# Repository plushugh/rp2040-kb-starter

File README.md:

# A Keyboard PCB Starter for the RaspberrySilicon RP2040 Microcontroller

## KiCad Requirements

I recommend KiCad version >= 8.0, and make sure you install the
[kiswitch](https://github.com/kiswitch/kiswitch) plugin (Version 2.4)
from the `Plugin and Content Manager`

I also recommend installing the kbplacer plugin for easy alignment of switch footprints

## Credits

Inspired by [Sleepdealr/RP2040-designguide](https://github.com/Sleepdealr/RP2040-designguide?tab=readme-ov-file)

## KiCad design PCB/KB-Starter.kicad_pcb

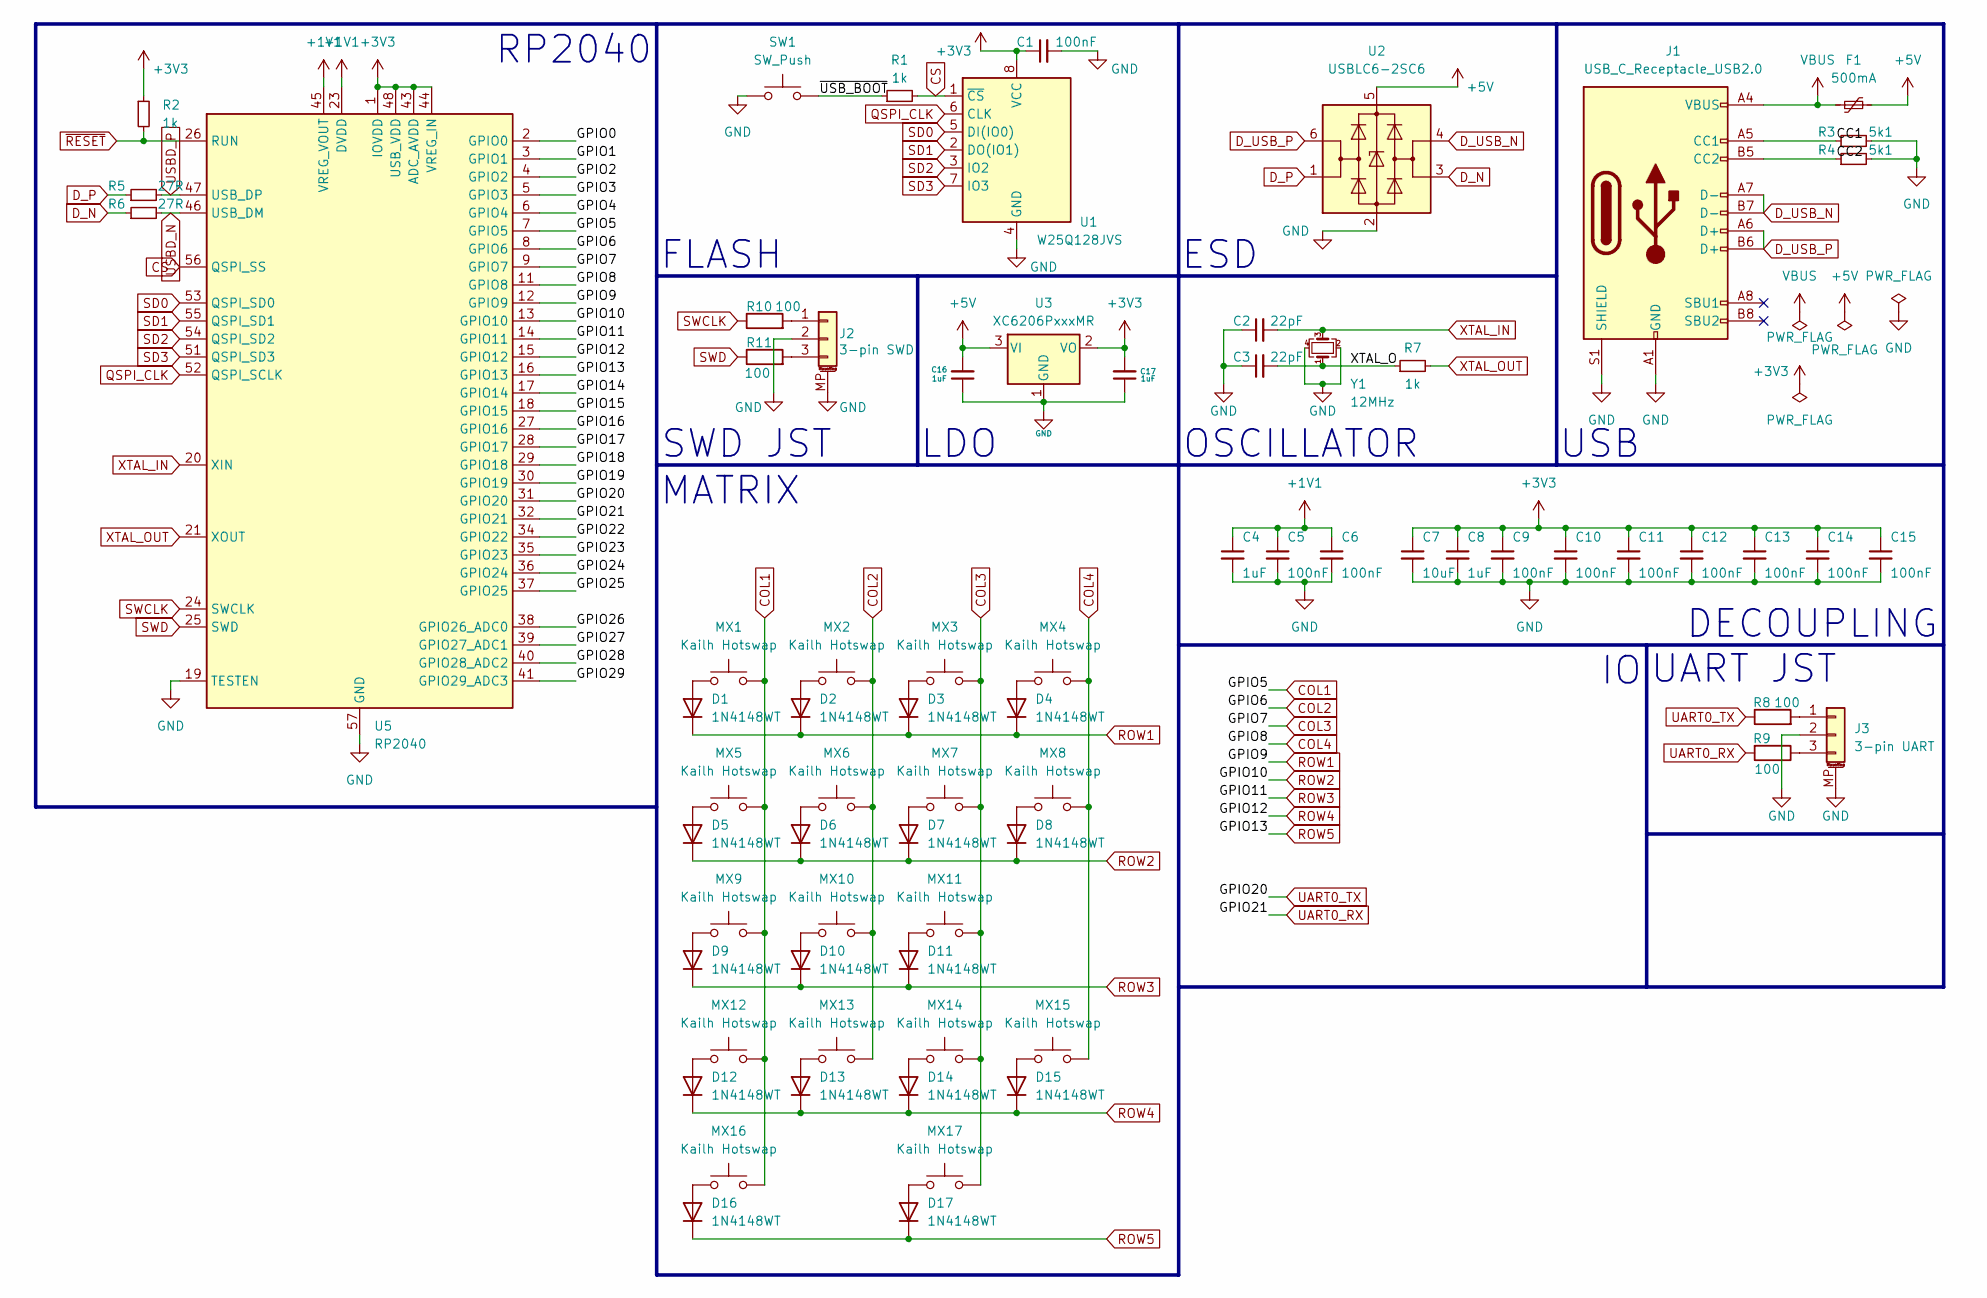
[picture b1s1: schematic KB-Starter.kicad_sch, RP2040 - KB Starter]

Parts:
C1, C5, C6, C9, C10, C11, C12, C13, C14, C15: 100nF; C_0402_1005Metric; LCSC C1525
C2, C3: 22pF; C_0402_1005Metric; LCSC C1555
C4, C8, C16, C17: 1uF; C_0402_1005Metric; LCSC C52923
C7: 10uF; C_0402_1005Metric; LCSC C15525
D1, D2, D3, D4, D5, D6, D7, D8, D9, D10, D11, D12, D13, D14, D15, D16, D17: 1N4148WT; D_SOD-523; LCSC C727112
F1: 500mA; Fuse_1206_3216Metric; LCSC C70076
J1: USB_C_Receptacle_USB2.0; USB_C_Receptacle_HRO_TYPE-C-31-M-12; LCSC C165948
J2: 3-pin SWD; JST_SH_BM03B-SRSS-TB_1x03-1MP_P1.00mm_Vertical
J3: 3-pin UART; JST_SH_BM03B-SRSS-TB_1x03-1MP_P1.00mm_Vertical
MX1, MX2, MX3, MX4, MX5, MX6, MX7, MX8, MX9, MX10, MX11, MX12, MX13, MX14, MX15, MX16, MX17: Kailh Hotswap; SW_Hotswap_Kailh_MX_1.00u; LCSC C5156480
R1, R2, R7: 1k; R_0402_1005Metric; LCSC C11702
R3, R4: 5k1; R_0402_1005Metric; LCSC C25905
R5, R6: 27R; R_0603_1608Metric; LCSC C25190
R8, R9, R10, R11: 100; R_0603_1608Metric
SW1: SW_Push; SW_SPST_PTS810; LCSC C221896
U1: W25Q128JVS; SOIC-8_5.23x5.23mm_P1.27mm; LCSC C131025
U2: USBLC6-2SC6; SOT-23-6; LCSC C2827654
U3: XC6206PxxxMR; SOT-23-3; LCSC C5250982
U5: RP2040; QFN-56-1EP_7x7mm_P0.4mm_EP3.2x3.2mm; LCSC C2040
Y1: 12MHz; Crystal_SMD_3225-4Pin_3.2x2.5mm; LCSC C9002

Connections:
+1V1: C4.1, C5.1, C6.1, U5.23 (DVDD), U5.45 (VREG_VOUT), U5.50 (DVDD)
+3V3: C1.1, C7.1, C8.1, C9.1, C10.1, C11.1, C12.1, C13.1, C14.1, C15.1, C17.2, R2.1, U1.8 (VCC), U3.2 (VO), U5.1 (IOVDD), U5.10 (IOVDD), U5.22 (IOVDD), U5.33 (IOVDD), U5.42 (IOVDD), U5.43 (ADC_AVDD), U5.44 (VREG_IN), U5.48 (USB_VDD), U5.49 (IOVDD)
+5V: C16.2, F1.2, U2.5 (VBUS), U3.3 (VI)
/CC1: J1.A5 (CC1), R3.1
/CC2: J1.B5 (CC2), R4.1
/GPIO0: U5.2 (GPIO0)
/GPIO1: U5.3 (GPIO1)
/GPIO2: U5.4 (GPIO2)
/GPIO3: U5.5 (GPIO3)
/GPIO4: U5.6 (GPIO4)
/GPIO14: U5.17 (GPIO14)
/GPIO15: U5.18 (GPIO15)
/GPIO16: U5.27 (GPIO16)
/GPIO17: U5.28 (GPIO17)
/GPIO18: U5.29 (GPIO18)
/GPIO19: U5.30 (GPIO19)
/GPIO22: U5.34 (GPIO22)
/GPIO23: U5.35 (GPIO23)
/GPIO24: U5.36 (GPIO24)
/GPIO25: U5.37 (GPIO25)
/GPIO26: U5.38 (GPIO26_ADC0)
/GPIO27: U5.39 (GPIO27_ADC1)
/GPIO28: U5.40 (GPIO28_ADC2)
/GPIO29: U5.41 (GPIO29_ADC3)
/XTAL_O: C3.2, R7.1, Y1.1
/~USB_BOOT: R1.1, SW1.2
COL1: MX1.2, MX5.2, MX9.2, MX12.2, MX16.2, U5.7 (GPIO5)
COL2: MX2.2, MX6.2, MX10.2, MX13.2, U5.8 (GPIO6)
COL3: MX3.2, MX7.2, MX11.2, MX14.2, MX17.2, U5.9 (GPIO7)
COL4: MX4.2, MX8.2, MX15.2, U5.11 (GPIO8)
CS: R1.2, U1.1 (~CS), U5.56 (QSPI_SS)
D_N: R6.1, U2.3 (I/O2)
D_P: R5.1, U2.1 (I/O1)
D_USB_N: J1.A7 (D-), J1.B7 (D-), U2.4 (I/O2)
D_USB_P: J1.A6 (D+), J1.B6 (D+), U2.6 (I/O1)
GND: C1.2, C2.1, C3.1, C4.2, C5.2, C6.2, C7.2, C8.2, C9.2, C10.2, C11.2, C12.2, C13.2, C14.2, C15.2, C16.1, C17.1, J1.A1 (GND), J1.A12 (GND), J1.B1 (GND), J1.B12 (GND), J1.S1 (SHIELD), J2.2, J2.MP (MountPin), J3.2, J3.MP (MountPin), R3.2, R4.2, SW1.1, U1.4 (GND), U2.2 (GND), U3.1 (GND), U5.19 (TESTEN), U5.57 (GND), Y1.2, Y1.4
unnamed: D1.2 (A), MX1.1
unnamed: D2.2 (A), MX2.1
unnamed: D3.2 (A), MX3.1
unnamed: D4.2 (A), MX4.1
unnamed: D5.2 (A), MX5.1
unnamed: D6.2 (A), MX6.1
unnamed: D7.2 (A), MX7.1
unnamed: D8.2 (A), MX8.1
unnamed: D9.2 (A), MX9.1
unnamed: D10.2 (A), MX10.1
unnamed: D11.2 (A), MX11.1
unnamed: D12.2 (A), MX12.1
unnamed: D13.2 (A), MX13.1
unnamed: D14.2 (A), MX14.1
unnamed: D15.2 (A), MX15.1
unnamed: D16.2 (A), MX16.1
unnamed: D17.2 (A), MX17.1
unnamed: J2.1, R10.2
unnamed: J2.3, R11.2
unnamed: J3.1, R8.2
unnamed: J3.3, R9.1
QSPI_CLK: U1.6 (CLK), U5.52 (QSPI_SCLK)
ROW1: D1.1 (K), D2.1 (K), D3.1 (K), D4.1 (K), U5.12 (GPIO9)
ROW2: D5.1 (K), D6.1 (K), D7.1 (K), D8.1 (K), U5.13 (GPIO10)
ROW3: D9.1 (K), D10.1 (K), D11.1 (K), U5.14 (GPIO11)
ROW4: D12.1 (K), D13.1 (K), D14.1 (K), D15.1 (K), U5.15 (GPIO12)
ROW5: D16.1 (K), D17.1 (K), U5.16 (GPIO13)
SD0: U1.5 (DI(IO0)), U5.53 (QSPI_SD0)
SD1: U1.2 (DO(IO1)), U5.55 (QSPI_SD1)
SD2: U1.3 (IO2), U5.54 (QSPI_SD2)
SD3: U1.7 (IO3), U5.51 (QSPI_SD3)
SWCLK: R10.1, U5.24 (SWCLK)
SWD: R11.1, U5.25 (SWD)
UART0_RX: R9.2, U5.32 (GPIO21)
UART0_TX: R8.1, U5.31 (GPIO20)
USBD_N: R6.2, U5.46 (USB_DM)
USBD_P: R5.2, U5.47 (USB_DP)
VBUS: F1.1, J1.A4 (VBUS), J1.A9 (VBUS), J1.B4 (VBUS), J1.B9 (VBUS)
XTAL_IN: C2.2, U5.20 (XIN), Y1.3
XTAL_OUT: R7.2, U5.21 (XOUT)
~RESET: R2.2, U5.26 (RUN)

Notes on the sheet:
MATRIX
ESD
UART JST
DECOUPLING
OSCILLATOR
USB
LDO
SWD JST
RP2040
FLASH

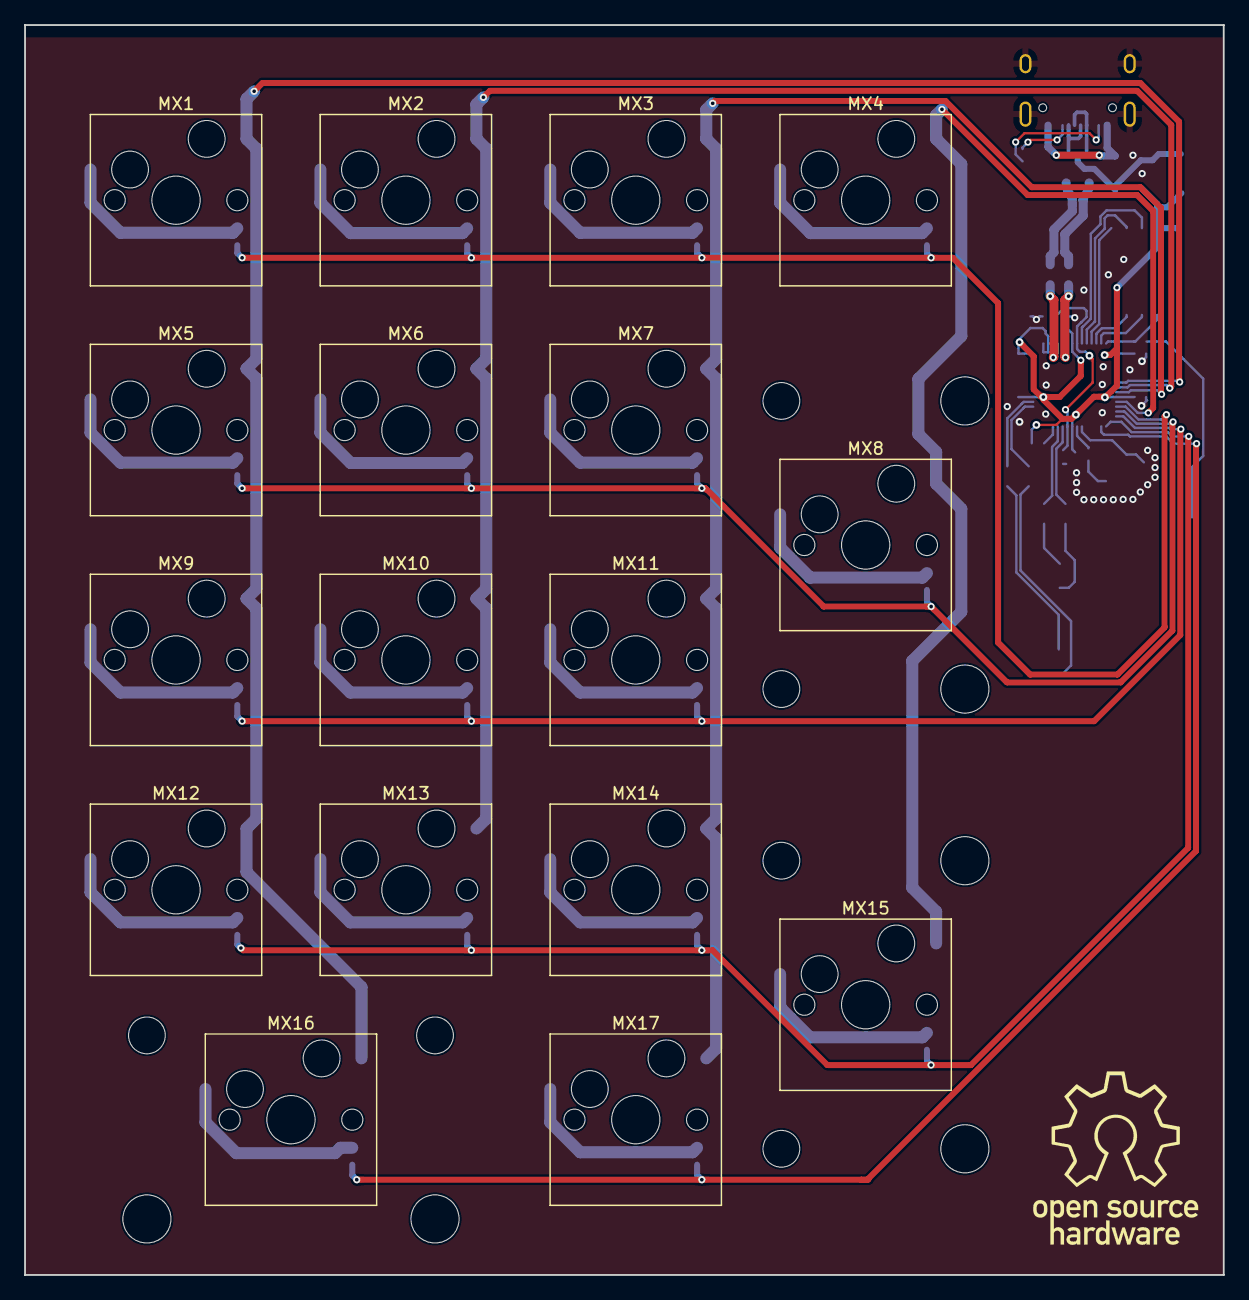
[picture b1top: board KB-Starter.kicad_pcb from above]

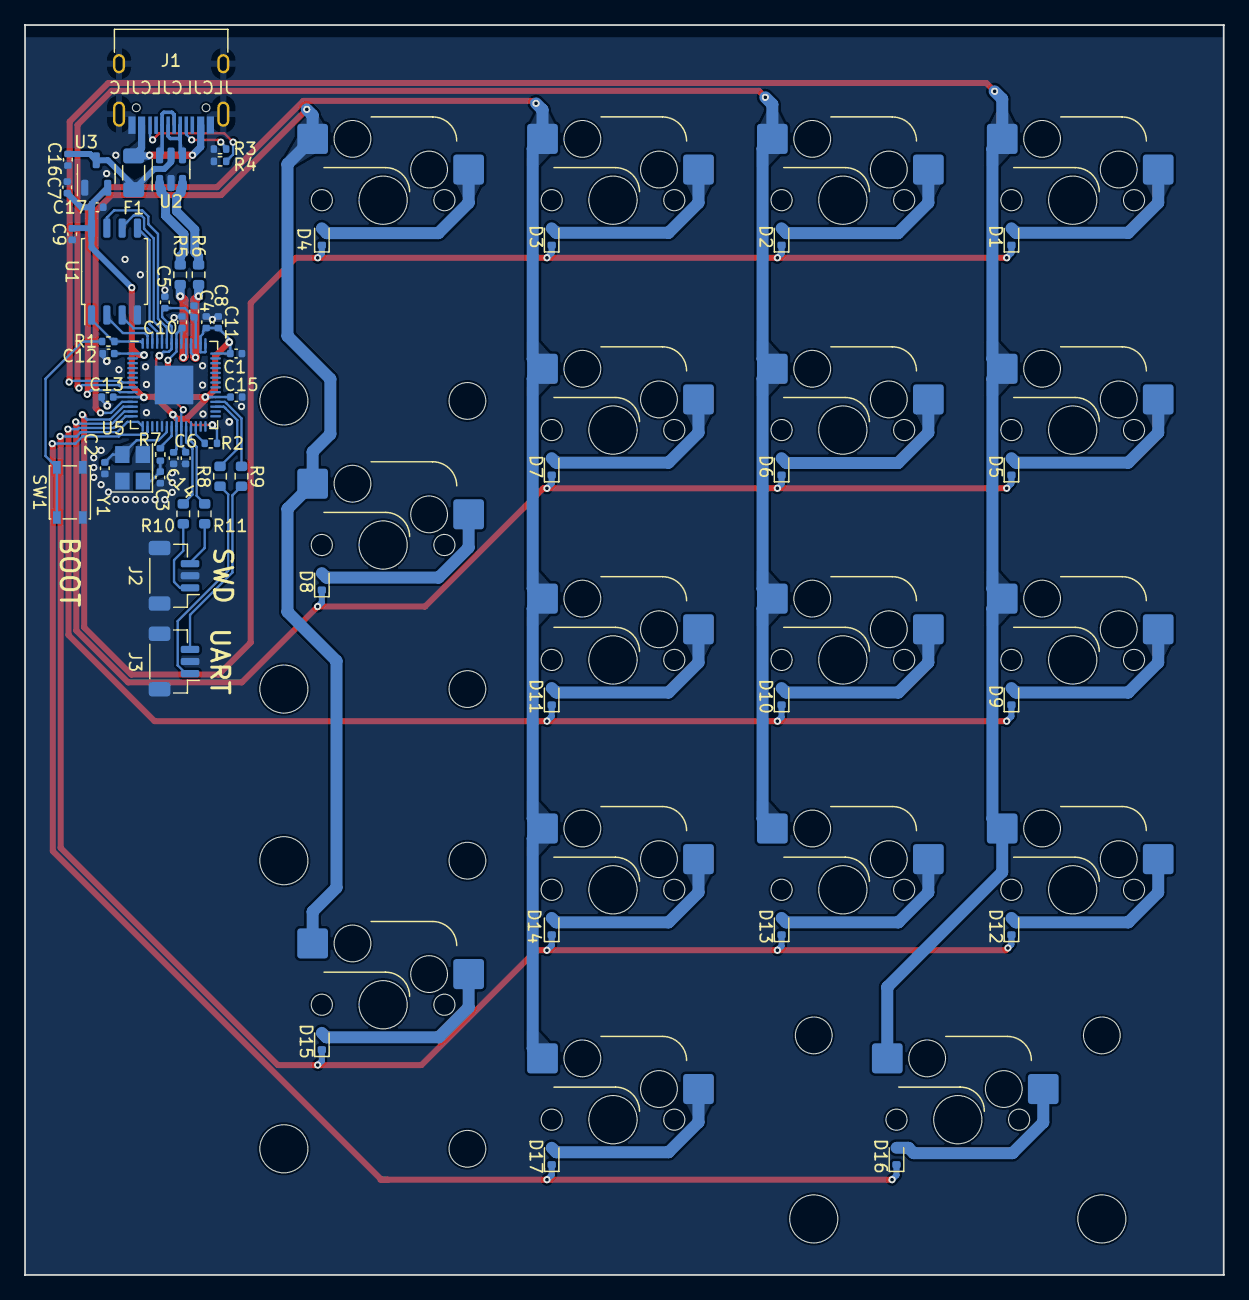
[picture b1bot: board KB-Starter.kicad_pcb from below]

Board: 2 copper layers, 99.3 x 103.6 mm, 75 parts (55 on the bottom side), 58 nets.

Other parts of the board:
STAB1, STAB2, STAB3: Stabilizer_Cherry_MX_2.00u

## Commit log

2024-02-13 init: basic mcu setup
2024-02-14 fix: USB data line impedance and length
2024-02-14 fix: reduce via-in-pads
2024-02-14 fix+feat: matrix fix + touchup
2024-02-14 feat: stabs
2024-02-14 fix: old footprints
2024-02-28 add missing 3d models, cleanup for KiCad 8, swd
2024-02-28 chore: bump README KiCad ver requirements
2024-02-29 feat: cleanup, graphics, JLCPCB DRU
